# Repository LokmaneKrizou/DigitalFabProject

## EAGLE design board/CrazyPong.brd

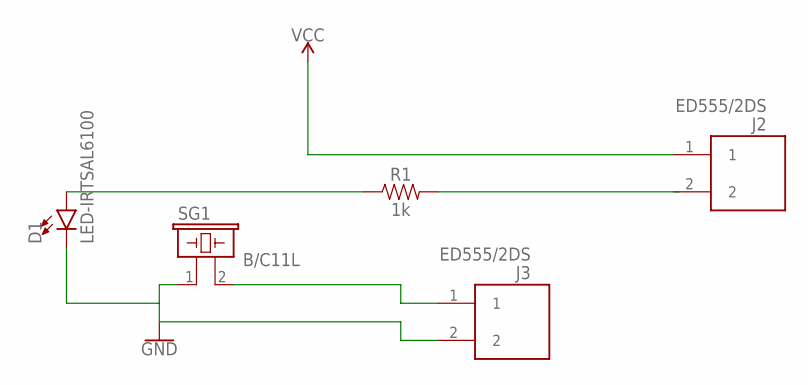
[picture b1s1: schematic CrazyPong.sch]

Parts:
D1: LED-IRTSAL6100; LED_5MM
J2, J3: ED555/2DS
R1: 1k; AXIAL-0.3-KIT
SG1: B/C11L

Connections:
GND: D1.K (C), J3.2, SG1.1
unnamed: J3.1, SG1.2
unnamed: D1.A, R1.P$1 (1)
VCC: J2.1

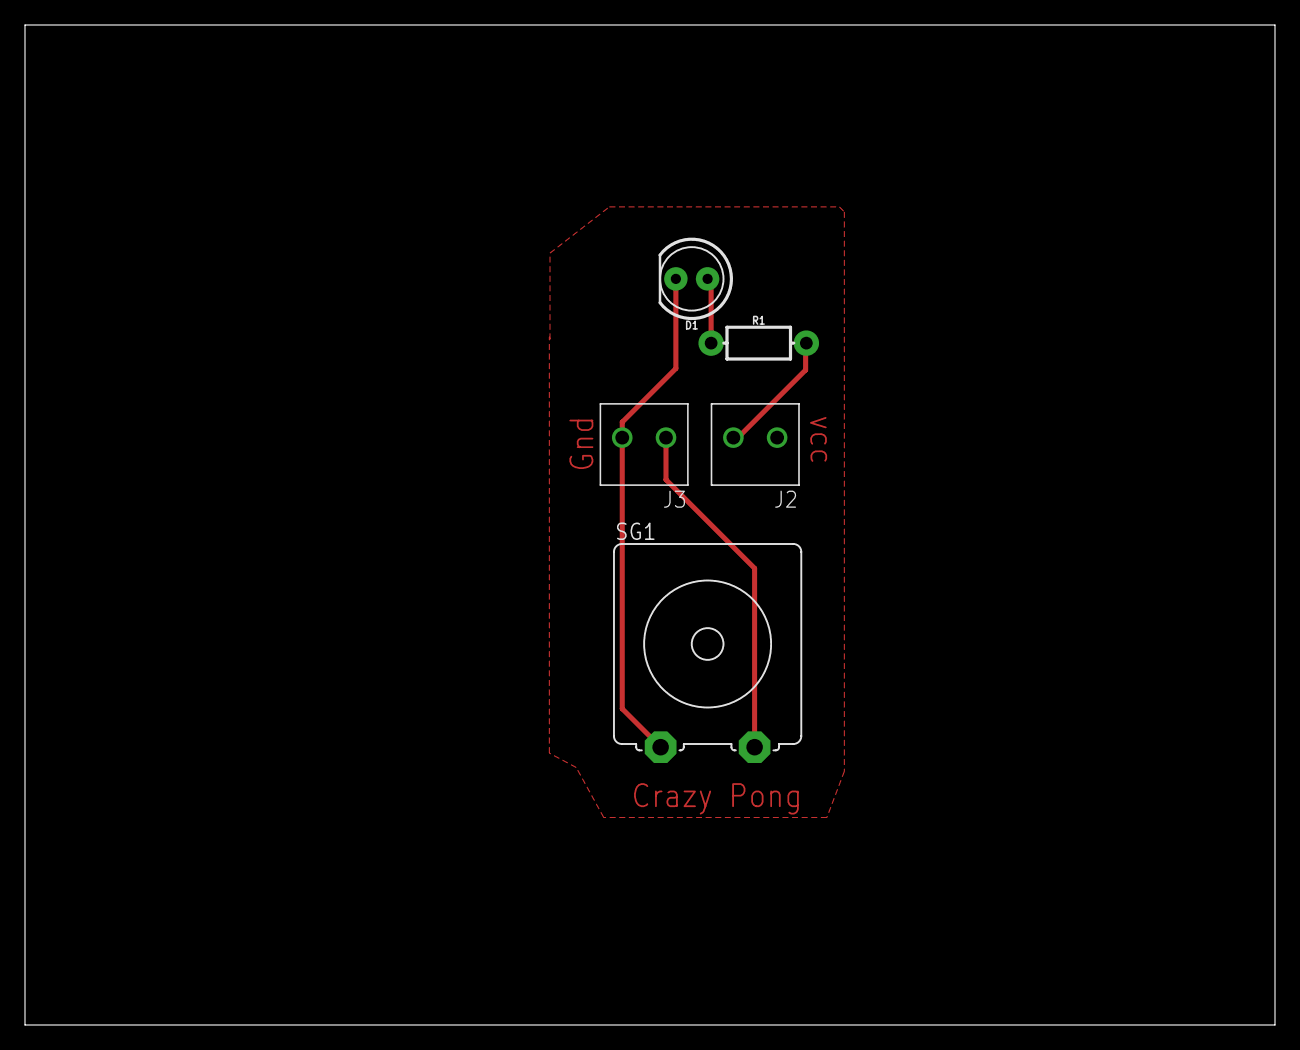
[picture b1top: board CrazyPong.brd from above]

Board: 2 copper layers, 100.0 x 80.0 mm, 5 parts (0 on the bottom side), 3 nets.

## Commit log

2018-05-08 system_box code
2018-06-12 added board

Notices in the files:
parts and their libraries:
SparkFun-LED: Licensing: Creative Commons ShareAlike 4.0 International - https://creativecommons.org/licenses/by-sa/4.0
